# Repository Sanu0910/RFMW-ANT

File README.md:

# RFMW-ANT: RF / Microwave Antenna Design Projects

RF / microwave antenna design projects, one folder per project under `projects/NN_name/`, built so each one can be **re-simulated, checked and fabricated**.

Tooling:
- EM simulation: [`docs/GDS2OPENEMS.md`](docs/GDS2OPENEMS.md) — openEMS FDTD + gds2openEMS, installed with `tools/install_gds2openems.sh`.
- EM simulation: [`docs/HERTZON.md`](docs/HERTZON.md) — Hertzon 3D full-wave FEM simulator (EMerge solver, MCP server), installed with `tools/install_hertzon.sh`.
- PCB: [`docs/KICAD_MCP.md`](docs/KICAD_MCP.md) — KiCad + KiCAD-MCP-Server headless, installed with `tools/install_kicad_mcp.sh`.
- Agentic CAD workspace: [`docs/BACKPLANE.md`](docs/BACKPLANE.md) — Backplane, installed with `tools/install_backplane.sh`.
- Reverse engineering: [`docs/REA.md`](docs/REA.md) — REA CLI/MCP, installed with `tools/install_rea.sh`.

## Projects

| # | Folder | Description | Band | Content |
|---|---|---|---|---|
| 01 | [`projects/01_xband-8way-msl-wpd-housing`](projects/01_xband-8way-msl-wpd-housing) | Machined housing CRL-XB-PD8-03 (V3) for the X-band 8-way microstrip Wilkinson divider on RO4350B 30 mil, 9 x H+S 23_SMA-50-0-272/133_N, BEL logo engraved | 8–12 GHz | base / lid with channel cage / gasket STEP, PCB V3 DXF (M2 holes) + Gerber/drill set, 2D channel-mode and Z0 checks, A3 drawings, report, BOM |
| 02 | [`projects/02_ls-crpa4-rf-module`](projects/02_ls-crpa4-rf-module) | CRL-LS-CRPA4: 4-ch active CRPA board (limiter + 2 LNA + 3 SAW per band, L1 + L2/L5 combined, NavIC S at lambda/2), combined L+S back cover for the BEL CRL 4-element L/S CRPA board | 1.16–1.61 / 2.49 GHz | Ø200 mm 4L PCB (DRC clean), fab package + BOM, combined back cover STEP, RF budget, drawings, design report |
| 03 | [`projects/03_crpa-processor-module`](projects/03_crpa-processor-module) | CRPA digitizer + anti-jam processor (power inversion / MVDR / STAP) behind the CRL-LS-CRPA4 antenna | 1.16–1.61 / 2.49 GHz | reference review, architecture options; GNSS_JAM_PRO v1.0 case (PocketSDR v2.3, CNC): STEP + drawings |
| 04 | [`projects/04_xband-msl-cal-line-baseplate`](projects/04_xband-msl-cal-line-baseplate) | Lightweight open base plates CRL-XB-CALP-15 / -65 for the X-band RO4350B MSL-SL-MSL THRU cal boards, 2 x H+S 23_SMA-50-0-272/133_N each (same as project 01) | 8–12 GHz | plate + assembly + exploded STEP, A3 CNC drawings with hole table, design report, BOM |

**Each project folder contains** `00_README.md` (what is where), `STATUS.md` (where it stands, open items, next step) and `CHANGELOG.md` (dated history).

## Quick start
Running locally (all tools + MCP servers) and pushing finished projects: see [`LOCAL_SETUP.md`](LOCAL_SETUP.md).

```bash
pip install -r docs/requirements.txt
```

## Conventions
[`docs/CONVENTIONS.md`](docs/CONVENTIONS.md) covers units, DXF layer naming, HFSS import, and how assumptions are flagged. The tool setup is in [`STATUS.md`](STATUS.md).

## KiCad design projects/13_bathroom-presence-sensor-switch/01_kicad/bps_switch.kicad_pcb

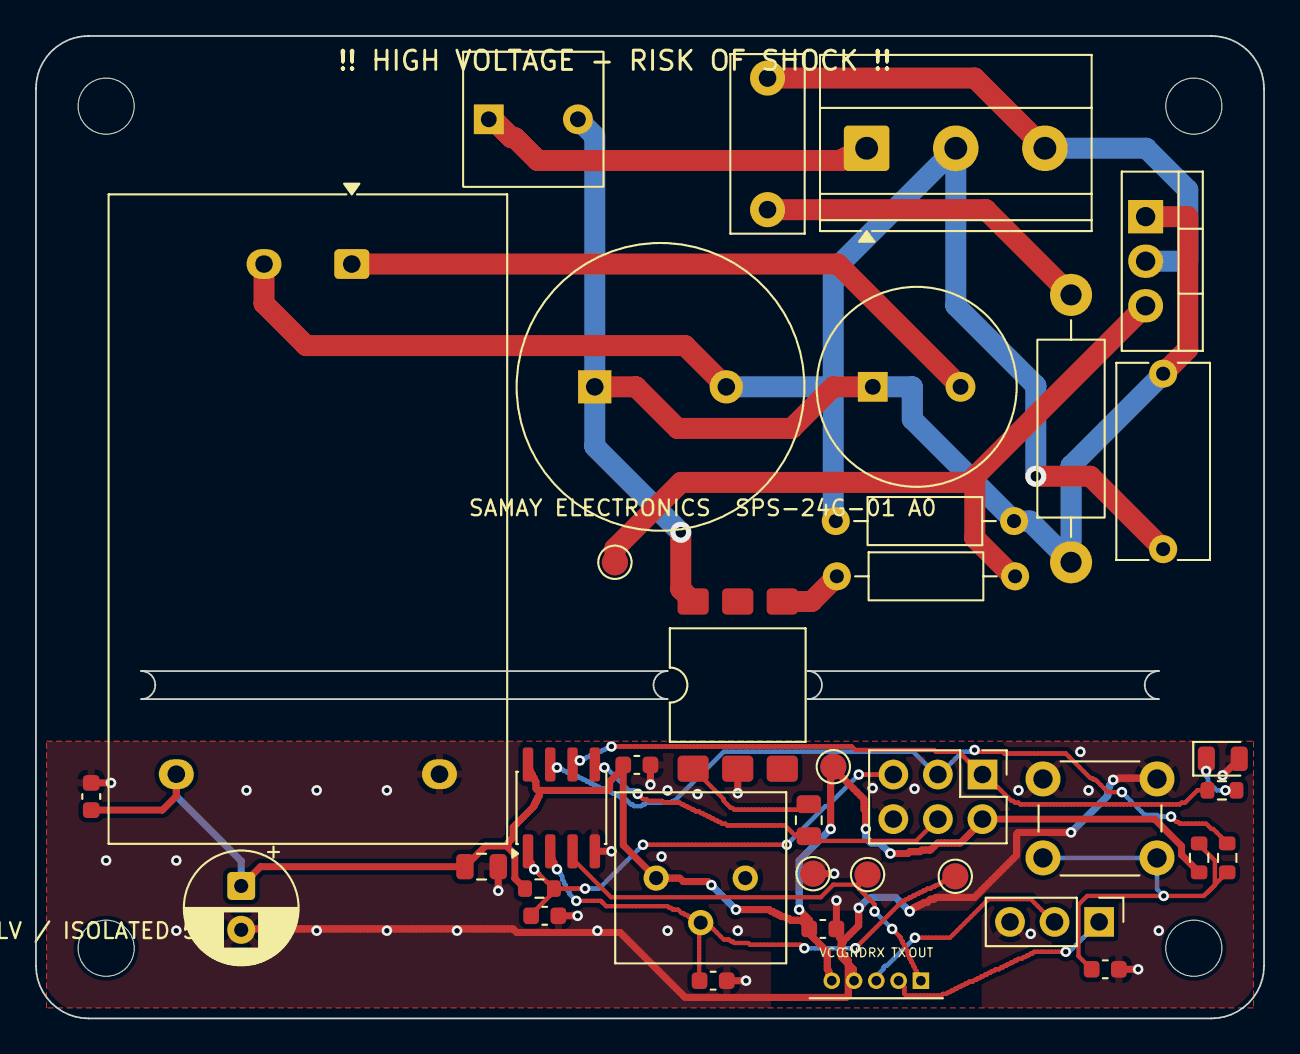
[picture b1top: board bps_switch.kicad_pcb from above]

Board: 2 copper layers, 70.0 x 56.0 mm, 41 parts (0 on the bottom side), 21 nets.

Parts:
C1, C4, C5, C6: 100nF; C_0603_1608Metric
C2: 10uF; C_0805_2012Metric
C3: 10nF; C_0603_1608Metric
CB1: 220uF/10V; CP_Radial_D6.3mm_P2.50mm
CB2: 100nF; C_0603_1608Metric
CS1: 10nF 400VAC; C_Rect_L10.0mm_W4.0mm_P7.50mm_FKS3_FKP3
CX1: 100nF X2; C_Rect_L11.0mm_W5.1mm_P10.00mm_MKT
D1: STATUS; LED_0805_2012Metric
F1: T500mA 250V; Fuse_TR5_P5.08mm
H1, H2, H3, H4: M3; MountingHole_3.2mm_M3
J1: L / N / LAMP; TerminalBlock_Phoenix_MKDS-1,5-3-5.08_1x03_P5.08mm_Horizont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
J2: AVR-ISP; PinHeader_2x03_P2.54mm_Vertical
J3: LD2410B; LD2410B_Module
J4: CFG UART; PinHeader_1x03_P2.54mm_Vertical
MOV1: 14D471K; Varistor_Disc_D16mm_P7.5mm
NTC1: 5D-9; NTC_Disc_D11mm_P5mm
PS1: HLK-PM01; Converter_ACDC_Hi-Link_HLK-PMxx
Q1: BTA16-600B; TO-220-3_Vertical
R1: 330R; R_0805_2012Metric
RB1: 1M; R_Axial_DIN0207_L6.3mm_D2.5mm_P10.16mm_Horizontal
RG1: 180R; R_Axial_DIN0207_L6.3mm_D2.5mm_P10.16mm_Horizontal
RL1: 1k; R_0603_1608Metric
RP1: 10k; R_0603_1608Metric
RR1: 10k; R_0603_1608Metric
RS1: 100R 2W; R_Axial_DIN0411_L9.9mm_D3.6mm_P15.24mm_Horizontal
RS2: 1k; R_0603_1608Metric
RV1: 10k; Potentiometer_Bourns_3386P_Vertical
SW1: OVERRIDE; SW_PUSH_6mm
TP1: +5V; TestPoint_Pad_D1.5mm
TP2: GND; TestPoint_Pad_D1.5mm
TP3: TRIAC_G; TestPoint_Pad_D1.5mm
TP4: RADAR_OUT; TestPoint_Pad_D1.5mm
TP5: DELAY_ADJ; TestPoint_Pad_D1.5mm
U1: ATtiny13A-SU; SOIC-8_3.9x4.9mm_P1.27mm
U2: MOC3063; SMDIP-6_W9.53mm_Clearance8mm

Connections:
+5V: C1.1, C2.1, C4.1, C5.1, CB1.1, J2.2, J3.5, PS1.4, RP1.1, RR1.1, RV1.1, TP1.1, U1.8
ACL_F: CX1.1, F1.2, MOV1.1, NTC1.1, Q1.1, RB1.1, RS1.1, U2.6
ACL_IN: F1.1, J1.1
ACN: CX1.2, J1.2, MOV1.2, PS1.2, RB1.2
BTN_SW: CB2.1, RP1.2, RS2.1, SW1.1
DELAY_ADJ: C6.1, RV1.2, TP5.1, U1.2
GND: C1.2, C2.2, C3.2, C4.2, C5.2, C6.2, CB1.2, CB2.2, D1.2, J2.6, J3.4, J4.3, PS1.3, RV1.3, SW1.2, TP2.1, U1.4, U2.2
LAMP: CS1.2, J1.3, Q1.2
LED_A: D1.1, RL1.2
MISO: J2.1, RL1.1, U1.6
MOSI: J2.4, R1.1, U1.5
OPTO_A: R1.2, U2.1
PSU_L: NTC1.2, PS1.1
RADAR_OUT: J3.1, TP4.1, U1.3
RADAR_RX: J3.3, J4.2
RADAR_TX: J3.2, J4.1
RESET: C3.1, J2.5, RR1.2, U1.1
SCK: J2.3, RS2.2, U1.7
SNUB_M: CS1.1, RS1.2
TRIAC_G: Q1.3, RG1.2, TP3.1
TRIAC_MT: RG1.1, U2.4

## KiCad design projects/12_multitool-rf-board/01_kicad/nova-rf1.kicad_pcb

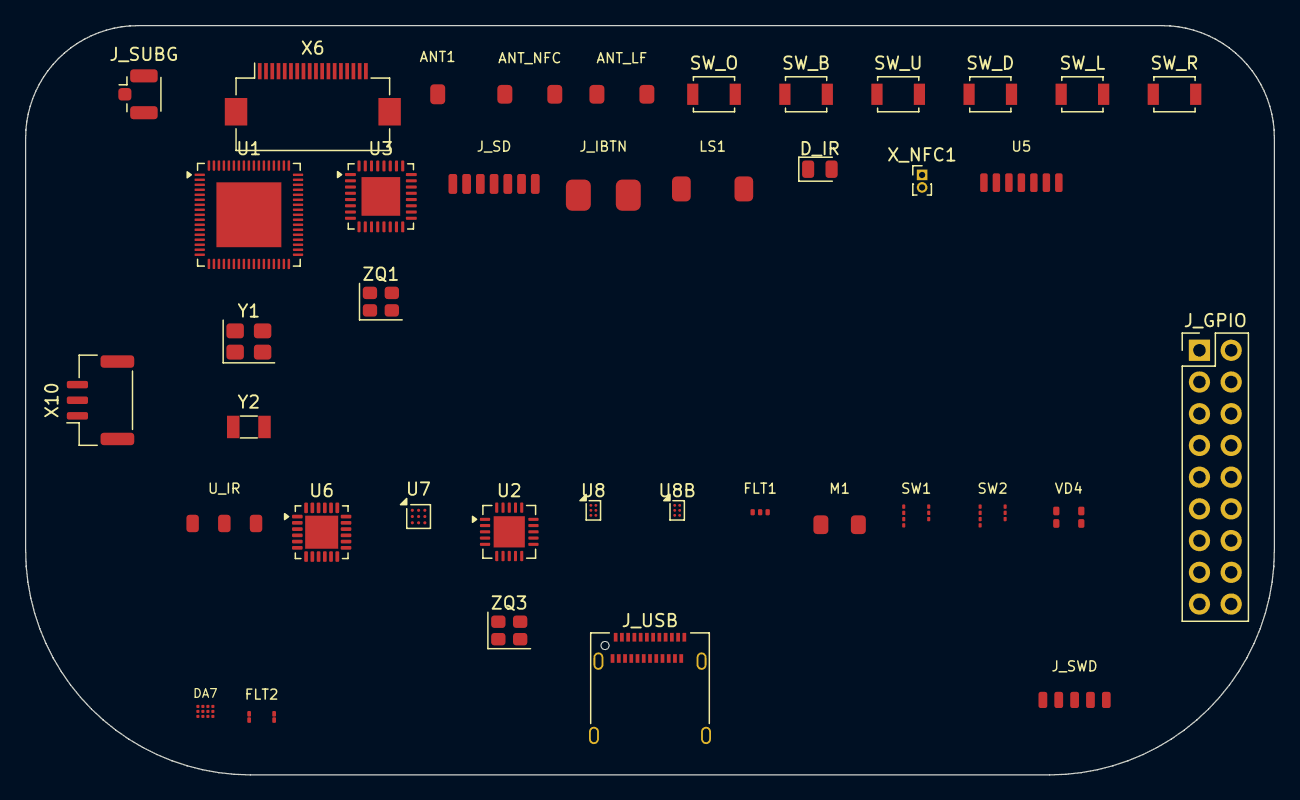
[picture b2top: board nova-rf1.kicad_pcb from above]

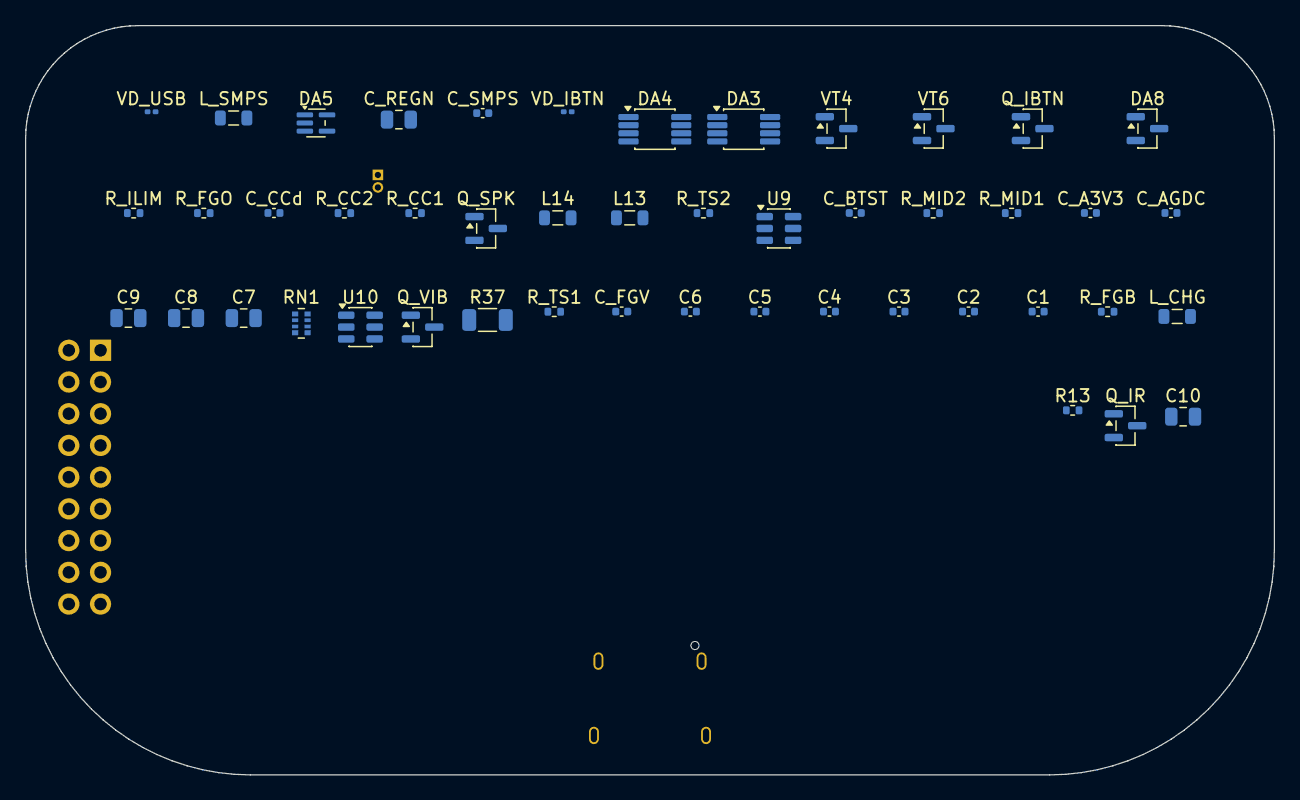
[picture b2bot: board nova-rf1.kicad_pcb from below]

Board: 4 copper layers, 100.0 x 60.0 mm, 87 parts (47 on the bottom side), 104 nets, no tracks yet.

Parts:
ANT1: 2.4GHz; Antenna_Chip
ANT_LF: 125kHz coil; RFID_125k_Coil
ANT_NFC: 13.56MHz loop; NFC_Loop_Antenna
C1, C2, C3, C4, C5, C6: 100nF; C_0402_1005Metric
C7, C8, C9, C10: 10uF; C_0805_2012Metric
C_A3V3: 1uF; C_0402_1005Metric
C_AGDC: 1uF; C_0402_1005Metric
C_BTST: 47nF; C_0402_1005Metric
C_CCd: 100nF; C_0402_1005Metric
C_FGV: 2.2uF; C_0402_1005Metric
C_REGN: 4.7uF; C_0805_2012Metric
C_SMPS: 2.2uF; C_0402_1005Metric
DA3, DA4: LMV358; VSSOP-8_3x3mm_P0.65mm
DA5: LMV331; SOT-353_SC-70-5
DA7: LP5562; LP5562_DSBGA12
DA8: RS3221-3.3; SOT-23
D_IR: IR LED x3; LED_0805_2012Metric
FLT1: BLE filter; RF_filter
FLT2: balun; Johanson_0310_Balun
J_GPIO: header 2x9; PinHeader_2x09_P2.54mm_Vertical
J_IBTN: iButton; iButton_Contacts
J_SD: microSD; microSD_7p
J_SUBG: ANT; U.FL_Hirose_U.FL-R-SMT-1_Vertical
J_SWD: SWD; TagConnect_TC2030
J_USB: USB-C; USB_C_Receptacle_Amphenol_12401610E4-2A
L13, L14: 470nH; L_0805_2012Metric
LS1: speaker; Speaker_2p
L_CHG: 2.2uH; L_0805_2012Metric
L_SMPS: 10uH; L_0805_2012Metric
M1: vibro; Vibro_2p
Q_IBTN: 1W driver; SOT-23
Q_IR: drive; SOT-23
Q_SPK: drive; SOT-23
Q_VIB: drive; SOT-23
R13: 56k; R_0402_1005Metric
R37: 10m; R_1206_3216Metric
RN1: 51x4; R_Array_Convex_4x0402
R_CC1, R_CC2: 5.1k; R_0402_1005Metric
R_FGB: 10k; R_0402_1005Metric
R_FGO: 10k; R_0402_1005Metric
R_ILIM: 1.1k; R_0402_1005Metric
R_MID1, R_MID2: 33k; R_0402_1005Metric
R_TS1: 5.23k; R_0402_1005Metric
R_TS2: 30.31k; R_0402_1005Metric
SW1, SW2: RFswitch; RF_Switch_TSNP9
SW_B: tact; SW_SPST_B3U-1000P
SW_D: tact; SW_SPST_B3U-1000P
SW_L: tact; SW_SPST_B3U-1000P
SW_O: tact; SW_SPST_B3U-1000P
SW_R: tact; SW_SPST_B3U-1000P
SW_U: tact; SW_SPST_B3U-1000P
U1: STM32WB55RG; QFN-68-1EP_8x8mm_P0.4mm_EP5.2x5.2mm
U2: CC1101; QFN-20-1EP_4x4mm_P0.5mm_EP2.5x2.5mm
U3: ST25R3916; QFN-32-1EP_5x5mm_P0.5mm_EP3.1x3.1mm
U5: ST7565R; Display_ST7565_FFC
U6: BQ25896; QFN-24-1EP_4x4mm_P0.5mm_EP2.65x2.65mm
U7: BQ27220; BGA-9_1.6x1.6mm_Layout3x3_P0.5mm
U8, U8B: LM3281; Texas_DSBGA-6_0.76x1.16mm_Layout2x3_P0.4mm
U9: loadsw; SOT-23-6
U10: ESD; SOT-23-6
U_IR: IR RX; TSOP_IR_3p
VD4: RGB LED; LED_RGB_4p
VD_IBTN: ESD; R_0201_0603Metric
VD_USB: ESD; R_0201_0603Metric
VT4: coildrv P; SOT-23
VT6: coildrv N; SOT-23
X6: FFC 18p; Hirose_FH12-18S-0.5SH_1x18-1MP_P0.50mm_Horizontal
X10: BAT+NTC; JST_GH_SM03B-GHS-TB_1x03-1MP_P1.25mm_Horizontal
X_NFC1: ANT conn; PinHeader_1x02_P1.00mm_Vertical
Y1: 32MHz; Crystal_SMD_3225-4Pin_3.2x2.5mm
Y2: 32.768kHz; Crystal_SMD_3215-2Pin_3.2x1.5mm
ZQ1: 27.12MHz; Crystal_SMD_2520-4Pin_2.5x2.0mm
ZQ3: 26MHz; Crystal_SMD_2520-4Pin_2.5x2.0mm

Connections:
+3V3: C1.1, C2.1, C3.1, C7.1, DA7.A2, DA7.C3, J_GPIO.1, J_SD.VDD, J_SWD.VCC, L13.2, SW1.VDD, SW2.VDD, U1.1, U1.13, U1.14, U1.30, U1.33, U1.44, U1.45, U1.55, U1.68, U2.4, U2.9, U2.11, U2.14, U2.15, U2.18, U3.1, U3.3, U3.7, U3.8, U3.9, U3.10, U3.11, U3.14, U5.VDD, U8.A1, U8.C1, U9.1, U_IR.VS, VD4.A
+3V3_EXT: L14.2, U8B.A1, X6.3
+3V3_PERIPH: C4.1, C10.1, U9.6
A3V3: C_A3V3.1, DA3.8, DA4.8, DA5.5, DA8.2, R_MID1.1
BLE_ANT: ANT1.1, FLT1.OUT
BTN_BACK: SW_B.1, U1.2
BTN_DOWN: SW_D.1, U1.50
BTN_LEFT: SW_L.1, U1.29
BTN_OK: SW_O.1, U1.5
BTN_RIGHT: SW_R.1, U1.46
BTN_UP: SW_U.1, U1.28
CC1101_CS: U1.61, U2.7
CC1101_GDO0: U1.16, U2.6
CC_DCOUPL: C_CCd.1, U2.5
CC_RBIAS: R13.1, U2.17
CC_XO1: U2.8, ZQ3.1
CC_XO2: U2.10, ZQ3.2
CHG_BTST: C_BTST.2, U6.21
CHG_ILIM: R_ILIM.1, U6.10
CHG_REGN: C_REGN.1, R_TS1.1, U6.22
CHG_SW: C_BTST.1, L_CHG.1, U6.19, U6.20
CHG_TS: R_TS1.2, R_TS2.1, U6.11
DISP_CS: U1.59, U5.CS
DISP_DI: U1.39, U5.A0
DISP_RST: U1.38, U5.RST
EXT_PA4: J_GPIO.4, U1.19
EXT_PA6: J_GPIO.3, U1.21
EXT_PA7: J_GPIO.2, U1.22
EXT_PB2: J_GPIO.6, U1.27
EXT_PB3: J_GPIO.5, U1.63
EXT_PC0: J_GPIO.9, U1.9
EXT_PC1: J_GPIO.8, U1.10
EXT_PC3: J_GPIO.7, U1.12
FG_BIN: R_FGB.1, U7.B1
FG_GPOUT: R_FGO.1, U7.A1
FG_VDD: C_FGV.1, R_FGO.2, U7.B3
GND: C1.2, C2.2, C3.2, C4.2, C5.2, C6.2, C7.2, C8.2, C9.2, C10.2, C_A3V3.2, C_AGDC.2, C_CCd.2, C_FGV.2, C_REGN.2, C_SMPS.2, DA3.4, DA4.4, DA5.2, DA7.B1, DA7.B2, DA7.B3, DA8.1, D_IR.1, FLT1.GND, FLT2.GND, J_GPIO.18, J_IBTN.GND, J_SD.VSS, J_SUBG.2, J_SWD.GND, J_USB.A1, J_USB.S1, LS1.-, M1.-, Q_IBTN.2, Q_IR.2, Q_SPK.2, Q_VIB.2, R13.2, R_CC1.2, R_CC2.2, R_FGB.2, R_ILIM.2, R_MID2.2, R_TS2.2, SW1.GND, SW2.GND, SW_B.2, SW_D.2, SW_L.2, SW_O.2, SW_R.2, SW_U.2, U1.32, U1.42, U1.69, U2.16, U2.19, U2.21, U3.6, U3.12, U3.16, U3.20, U3.21, U3.26, U3.33, U5.VSS, U6.9, U6.17, U6.18, U6.25, U7.B2, U7.C2, U8.C2, U8B.C2, U9.2, U10.2, U_IR.GND, VD_IBTN.2, VD_USB.2, VT6.2, X6.6, X6.8, X10.3
HSE_IN: U1.35, Y1.1
HSE_OUT: U1.34, Y1.2
I2C_PWR_SCL: DA7.C2, J_GPIO.15, U1.24, U6.5, U7.A3
I2C_PWR_SDA: DA7.C1, J_GPIO.14, U1.51, U6.6, U7.A2
IBTN: J_IBTN.DATA, Q_IBTN.1, U1.48, VD_IBTN.1, X6.14
IR_LED_A: D_IR.2, Q_IR.3
IR_RX: U1.15, U_IR.OUT, X6.17
IR_TX: Q_IR.1, U1.7, X6.16
LED_B: DA7.A4, VD4.B
LED_G: DA7.B4, VD4.G
LED_R: DA7.C4, VD4.R
LF_A1: DA3.1, DA3.5
LF_A2: DA3.7, DA4.3
LF_A3: DA4.1, DA4.5
LF_COIL_P: ANT_LF.1, VT4.3, VT6.3
LF_ENV: DA4.7, DA5.1
LF_MID: DA3.2, DA5.3, R_MID1.2, R_MID2.1
LF_RX: ANT_LF.2, DA3.3
LSE_IN: U1.3, Y2.1
LSE_OUT: U1.4, Y2.2
NFC_AGDC: C_AGDC.1, U3.24
NFC_ANT_N: ANT_NFC.2, X_NFC1.2
NFC_ANT_P: ANT_NFC.1, X_NFC1.1
NFC_CS: RN1.4, U1.40, U3.29, X6.4
NFC_XTAL1: U3.5, ZQ1.1
NFC_XTAL2: U3.4, ZQ1.2
NRST: J_SWD.NRST, U1.8
PERIPH_EN: U1.18, U8B.C1, U9.3
RFID_CARRIER: U1.17, U3.27, X6.12, X6.18
RFID_CARRIER_OUT: U1.57, VT4.1, X6.11
RFID_RF_IN: DA5.4, U1.26, X6.5
RF_SW_0: SW1.V1, SW2.V1, U1.25
RF_SW_1: SW1.V2, SW2.V2
SD_CD: J_SD.CD, U1.58
SD_CS: J_SD.CS, U1.60
SMPS_FB: C_SMPS.1, L_SMPS.2, U1.41
SMPS_LX: L_SMPS.1, U1.43
SPEAKER: Q_SPK.1, U1.6, X6.15
SPI_D_MISO: J_SD.DO, U1.11
SPI_D_MOSI: J_SD.DI, U1.49, U5.SI
SPI_D_SCK: J_SD.CLK, U1.62, U5.SCL
SPI_R_MISO: RN1.2, U1.64, U2.2, U3.32, X6.9
SPI_R_MOSI: RN1.3, U1.65, U2.20, U3.31, X6.13
SPI_R_SCK: RN1.1, U1.20, U2.1, U3.30, X6.7
SPK_DRV: LS1.+, Q_SPK.3
SUBG_ANT: J_SUBG.1, SW2.RFin
SUBG_F1: SW1.RF1, SW2.RF1
SUBG_F2: SW1.RF2, SW2.RF2
SUBG_RF_N: FLT2.BAL2, U2.13
SUBG_RF_P: FLT2.BAL1, U2.12
SUBG_SE: FLT2.UNBAL, SW1.RFin
SWCLK: J_GPIO.10, J_SWD.SWCLK, U1.56
SWDIO: J_GPIO.11, J_SWD.SWDIO, U1.54
SW_L13: L13.1, U8.B2
SW_L14: L14.1, U8B.B2
UART_RX: J_GPIO.13, U1.67
UART_TX: J_GPIO.12, U1.66
USB_CC1: J_USB.A5, R_CC1.1
USB_CC2: J_USB.B5, R_CC2.1
USB_DM: J_USB.A7, U1.52, U10.1, U10.6, VD_USB.1
USB_DP: J_USB.A6, U1.53, U10.3, U10.4
VBAT: C6.1, C9.1, R37.1, U6.13, U6.14, U7.C3, X10.1
VBAT_SNS: R37.2, U7.C1
VBUS: J_GPIO.16, J_USB.A4, U6.1, U10.5
VIBRO: J_GPIO.17, Q_VIB.1, U1.23, X6.10
VIBRO_DRV: M1.+, Q_VIB.3
VSYS: C5.1, C8.1, DA8.3, L_CHG.2, U6.15, U6.16, U8.A2, U8.B1, U8B.A2, U8B.B1, VT4.2, X6.1, X6.2

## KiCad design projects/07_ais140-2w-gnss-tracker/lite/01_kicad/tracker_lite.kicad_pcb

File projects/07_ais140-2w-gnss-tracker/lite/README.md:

# Samay Track Lite (preliminary)

A low-cost 4G Cat-1 + 2G bike tracker. **Not designed yet.** This folder holds the plan, the preliminary BOM and the poster.

| File | Content |
|---|---|
| `LITE_BOM_preliminary.csv` | Candidate parts with estimated 1k prices (≈ ₹1,362 per unit) |
| `poster_lite.html` / `SamayTrackLite_poster.png` / `.pdf` | Launch poster (₹3,499 incl. year 1, then ₹999/yr) |
| `../premium/07_marketing/SamayTrack_Lite_Plan.pdf` | 3-page plan: design, cost, price, money, timeline |

## BOM summary (estimate at 1,000 pcs, INR, excl. GST)

| Group | Main parts | ₹ |
|---|---|---|
| Modules | A7672S LTE Cat-1 + GSM (runs the firmware) · Quectel L76K GPS + BeiDou | 780 |
| ICs | LIS2DH12 accelerometer · LMR16010 60 V buck · BQ21040 charger · TLV75533 LDO · W25Q32 flash | 151 |
| Protection + I/O | SMBJ33CA TVS · reverse-polarity MOSFET · PTC fuse · SIM ESD · input clamps · relay MOSFET · LEDs | 35 |
| Connectors | nano-SIM, battery, harness, IPEX | 26 |
| Antennas | 25 mm GNSS ceramic patch · LTE FPC | 70 |
| Battery | 300 mAh Li-po with PCM (BIS registered) | 55 |
| Passives | ≈ 60 R/C/L + 2× 220 µF bulk caps for 2G bursts | 45 |
| PCB + SMT | 2-layer ≈ 50 × 35 mm, single-sided | 65 |
| Box build | IP65 enclosure, 4-wire harness with fuse, packaging | 135 |
| **Total** | | **≈ 1,362** |

Options:
- NavIC GNSS: + ₹300–400
- SOS push-button: + ₹25
- MFF2 eSIM instead of the nano-SIM holder

Prices are typical distributor or China-sourcing prices from memory, not quotes. Get real quotes before you commit.

**Design note:** in 2G the modem draws ≈ 2 A peaks, so the power path needs the battery plus the bulk capacitors. Size the buck and the charger for that.

Regenerate the poster (render taller and crop, because the headless window is ≈ 90 px shorter than `--window-size`):

    chrome --headless=new --force-device-scale-factor=2 --window-size=1200,1760 --screenshot=raw.png poster_lite.html   # crop to 2400 × 3280
    chrome --headless=new --no-pdf-header-footer --print-to-pdf=SamayTrackLite_poster.pdf poster_lite.html

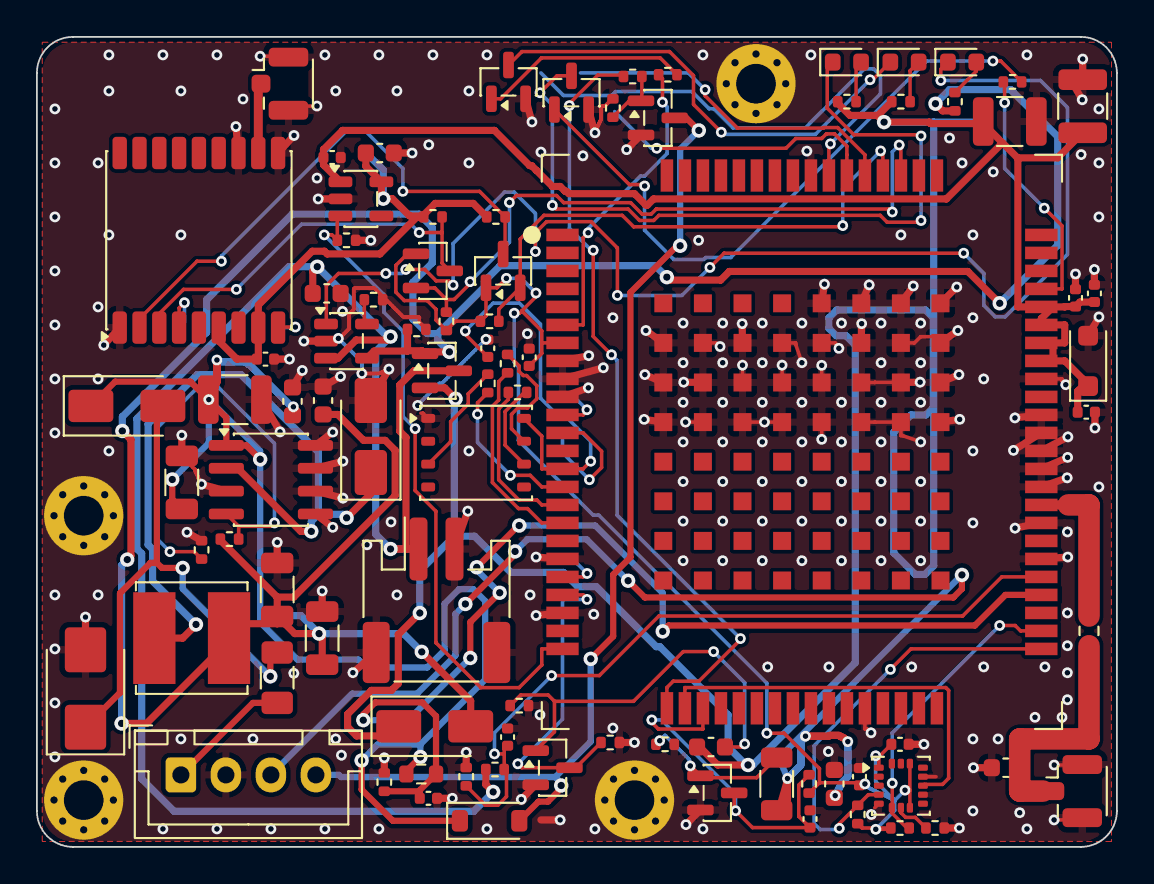
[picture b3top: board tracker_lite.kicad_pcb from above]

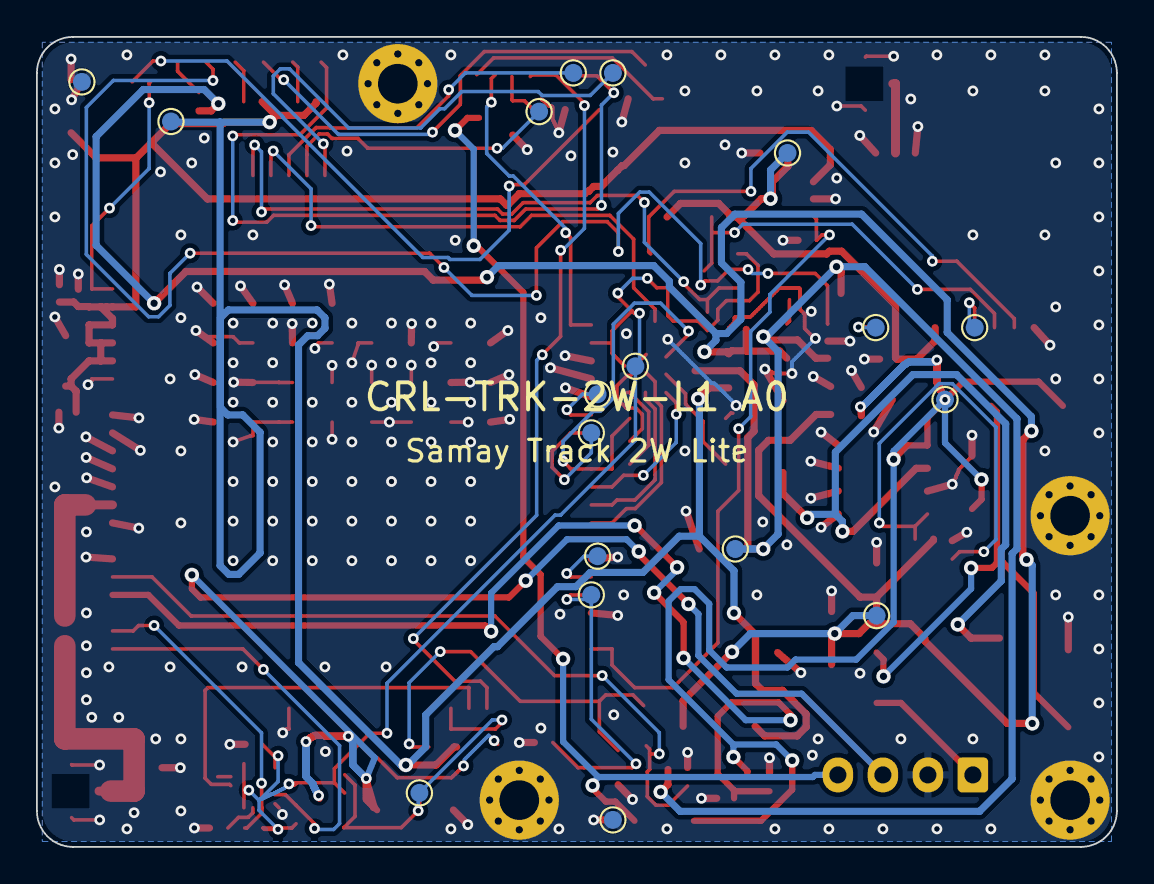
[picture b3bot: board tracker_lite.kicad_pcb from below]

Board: 2 copper layers, 60.0 x 45.0 mm, 109 parts (18 on the bottom side), 59 nets.

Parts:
C1: 10uF/50V; C_1210_3225Metric
C2: 4.7uF/50V; C_1206_3216Metric
C3: 100nF/50V; C_0603_1608Metric
C4, C5: 22uF/10V; C_1206_3216Metric
C6, C7: 4.7uF/10V; C_0603_1608Metric
C8, C9: 100uF/6.3V; C_1210_3225Metric
C10, C13, C14, C17, C22, C26: 100nF; C_0402_1005Metric
C11: 33pF; C_0402_1005Metric
C12: 10pF; C_0402_1005Metric
C15, C20, C27: 1uF; C_0402_1005Metric
C16, C21: 10uF/10V; C_0603_1608Metric
C19: DNP; C_0603_1608Metric
C28: 10nF/100V; C_0603_1608Metric
C29: 1nF; C_0402_1005Metric
D1: SMBJ24CA; D_SMB
D2, D3, D4: SS34; D_SMA
D5: SMF5.0A; D_SOD-123F
D6: 1N4148W; D_SOD-123
D7: YELLOW; LED_0603_1608Metric
D8: GREEN; LED_0603_1608Metric
D9: RED; LED_0603_1608Metric
F1: 2A; Fuse_1206_3216Metric
H1, H2, H3, H4: M2; MountingHole_2.2mm_M2_Pad_Via
J1: VEHICLE 4P; JST_XH_B4B-XH-A_1x04_P2.50mm_Vertical
J2: LiPo 300mAh; JST_PH_S2B-PH-SM4-TB_1x02-1MP_P2.00mm_Horizontal
J4: LTE ANT; U.FL_Hirose_U.FL-R-SMT-1_Vertical
J5: GNSS ANT; U.FL_Hirose_U.FL-R-SMT-1_Vertical
L1: 22uH; L_Bourns_SRN6045TA
Q1: AO3401A; SOT-23
Q2: 2N7002; SOT-23
Q3, Q4: BSS138; SOT-23
Q5, Q7, Q8: MMBT3904; SOT-23
Q6: AO3400A; SOT-23
R1: 2.61k; R_0402_1005Metric
R2, R30, R32, R33: 1k; R_0402_1005Metric
R3: 6.8k; R_0402_1005Metric
R4, R8, R15, R26, R28: 100k; R_0402_1005Metric
R5: 1M; R_0603_1608Metric
R6: 33k; R_0402_1005Metric
R7: 300k; R_0402_1005Metric
R9: 220k; R_0402_1005Metric
R10: 0R; R_0402_1005Metric
R11, R12, R13: 22R; R_0402_1005Metric
R14: 0R; R_0603_1608Metric
R18, R19, R20, R21, R25, R34: 10k; R_0402_1005Metric
R22, R23, R29, R31: 4.7k; R_0402_1005Metric
R24: 47k; R_1206_3216Metric
R27: 100R; R_0402_1005Metric
TP1: MDM_PWRKEY; TestPoint_Pad_D1.0mm
TP2: MDM_RESET_N; TestPoint_Pad_D1.0mm
TP3: MDM_USB_VBUS; TestPoint_Pad_D1.0mm
TP4: MDM_USB_DP; TestPoint_Pad_D1.0mm
TP5: MDM_USB_DM; TestPoint_Pad_D1.0mm
TP6: MDM_DBG_TX; TestPoint_Pad_D1.0mm
TP7: MDM_DBG_RX; TestPoint_Pad_D1.0mm
TP8: GNSS_RST_N; TestPoint_Pad_D1.0mm
TP9: GNSS_1PPS; TestPoint_Pad_D1.0mm
TP10: VIN_PROT; TestPoint_Pad_D1.0mm
TP11: V4_BUCK; TestPoint_Pad_D1.0mm
TP12: VSYS; TestPoint_Pad_D1.0mm
TP13: VBAT; TestPoint_Pad_D1.0mm
TP14: MDM_1V8; TestPoint_Pad_D1.0mm
TP15: +3V3_GNSS; TestPoint_Pad_D1.0mm
TP16, TP17: GND; TestPoint_Pad_D1.0mm
TP18: IGN_DET_N; TestPoint_Pad_D1.0mm
U1: XL1509-ADJ; SOIC-8_3.9x4.9mm_P1.27mm
U2: MCP73831-2; SOT-23-5
U3: EC200U-CN; Quectel_EC200U_LCC-144
U5: L76K; Quectel_L76K
U6: AP2112K-3.3; SOT-23-5
U7: LIS3DH; LGA-16_3x3mm_P0.5mm_LayoutBorder3x5y
U8: MFF2 eSIM; MFF2_eSIM_DFN-8_6x5mm

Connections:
+3V3_GNSS: C21.1, C22.1, R19.1, R21.1, TP15.1, U5.6, U5.8, U6.5
ACC_INT: U3.26, U7.11
ACC_SA0: R34.1, U7.7
BUCK_FB: R1.2, R2.1, U1.4
BUCK_SW: D3.1, L1.1, U1.2
CHG_PROG: R3.1, U2.5
CHG_STAT: D9.1, U2.1
GND: C1.2, C2.2, C3.2, C4.2, C5.2, C6.2, C7.2, C8.2, C9.2, C10.2, C11.2, C12.2, C13.2, C14.2, C15.2, C17.2, C19.2, C20.2, C21.2, C22.2, C26.2, C27.2, C28.2, C29.2, D1.2, D3.2, D5.2, H1.1, H2.1, H3.1, H4.1, J1.2, J2.2, J2.MP, J4.2, J5.2, Q2.2, Q5.2, Q6.2, Q7.2, Q8.2, R2.2, R3.2, R4.2, R6.2, R8.2, R9.2, R10.2, R15.2, R25.2, R28.2, R34.2, TP16.1, TP17.1, U1.3, U1.5, U1.6, U1.7, U1.8, U2.2, U3.8, U3.9, U3.10, U3.19, U3.22, U3.36, U3.46, U3.48, U3.50, U3.51, U3.52, U3.53, U3.54, U3.56, U3.72, U3.85, U3.86, U3.87, U3.88, U3.89, U3.90, U3.91, U3.92, U3.93, U3.94, U3.95, U3.96, U3.97, U3.98, U3.99, U3.100, U3.101, U3.102, U3.103, U3.104, U3.105, U3.106, U3.107, U3.108, U3.109, U3.110, U3.111, U3.112, U5.1, U5.10, U5.12, U6.2, U7.5, U7.10, U7.12, U8.1
GNSS_1PPS: TP9.1, U5.4
GNSS_EN: R15.1, U3.24, U6.3
GNSS_RF: J5.1, U5.11
GNSS_RST_N: TP8.1, U5.9
GNSS_RXD: Q3.3, R19.2, U5.3
GNSS_TXD: Q4.3, R21.2, U5.2
I2C_SCL: R23.2, U3.41, U7.4
I2C_SDA: R22.2, U3.42, U7.6
IGN_B: Q5.1, R24.2, R25.1
IGN_DET_N: C29.1, Q5.3, R26.2, TP18.1, U3.27
IGN_RAW: C28.1, J1.3, R24.1
LED_CHG_A: D9.2, R33.2
LED_NET_A: D7.2, R30.2
LED_NET_K: D7.1, Q7.3
LED_PWR_A: D8.2, R32.2
LED_PWR_K: D8.1, Q8.3
LTE_RF: C19.1, J4.1, R14.2
LTE_RF_M: R14.1, U3.49
MDM_1V8: C15.1, C26.1, C27.1, Q3.1, Q4.1, R18.1, R20.1, R22.1, R23.1, R26.1, TP14.1, U3.7, U7.1, U7.8, U7.14
MDM_DBG_RX: TP7.1, U3.11
MDM_DBG_TX: TP6.1, U3.12
MDM_PWRKEY: Q2.3, R10.1, TP1.1, U3.21
MDM_RESET_N: TP2.1, U3.20
MDM_RX_1V8: Q4.2, R20.2, U3.68
MDM_STATUS: R31.1, U3.61
MDM_TX_1V8: Q3.2, R18.2, U3.67
MDM_USB_DM: TP5.1, U3.70
MDM_USB_DP: TP4.1, U3.69
MDM_USB_VBUS: TP3.1, U3.71
NET_B: Q7.1, R29.2
NET_STATUS: R29.1, U3.6
PWRKEY_G: C16.2, Q2.1, R9.1
RELAY_CTL: R27.1, U3.25
RELAY_G: Q6.1, R27.2, R28.1
RELAY_OUT: D6.2, J1.4, Q6.3
SIM_CLK: R12.2, U8.6
SIM_CLK_M: R12.1, U3.16
SIM_DATA: R11.2, U8.3
SIM_DATA_M: R11.1, U3.15
SIM_RST: R13.2, U8.7
SIM_RST_M: R13.1, U3.17
SIM_VDD: C17.1, U3.14, U8.8
STAT_B: Q8.1, R31.2
V4_BUCK: C4.1, C5.1, C6.1, D4.2, L1.2, Q1.1, R1.1, R4.1, R33.1, TP11.1, U2.4
VBAT: C7.1, J2.1, Q1.3, R7.1, TP13.1, U2.3
VBAT_SENSE: C14.1, R7.2, R8.1, U3.45
VIN_F: D1.1, D2.2, F1.2
VIN_PROT: C1.1, C2.1, C3.1, D2.1, D6.1, R5.1, TP10.1, U1.1
VIN_RAW: F1.1, J1.1
VIN_SENSE: C13.1, R5.2, R6.1, U3.44
VSYS: C8.1, C9.1, C10.1, C11.1, C12.1, C16.1, C20.1, D4.1, D5.1, Q1.2, R30.1, R32.1, TP12.1, U3.57, U3.58, U3.59, U3.60, U6.1

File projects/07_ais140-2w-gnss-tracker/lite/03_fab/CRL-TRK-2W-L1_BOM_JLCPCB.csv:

Comment,Designator,Footprint,LCSC Part #,Manufacturer Part Number
10uF/50V,C1,C_1210_3225Metric,,1210 MLCC X5R/X7R
4.7uF/50V,C2,C_1206_3216Metric,,1206 MLCC X5R/X7R
100nF/50V,C3,C_0603_1608Metric,,0603 MLCC X5R/X7R
22uF/10V,"C4,C5",C_1206_3216Metric,,1206 MLCC X5R/X7R
4.7uF/10V,"C6,C7",C_0603_1608Metric,,0603 MLCC X5R/X7R
100uF/6.3V,"C8,C9",C_1210_3225Metric,,1210 MLCC X5R/X7R
100nF,"C10,C13,C14,C17,C22,C26",C_0402_1005Metric,,0402 MLCC X5R/X7R
33pF,C11,C_0402_1005Metric,,0402 C0G 50V
10pF,C12,C_0402_1005Metric,,0402 C0G 50V
1uF,"C15,C20,C27",C_0402_1005Metric,,0402 MLCC X5R/X7R
10uF/10V,"C16,C21",C_0603_1608Metric,,0603 MLCC X5R/X7R
10nF,C23,C_0402_1005Metric,,0402 MLCC X5R/X7R
10nF/100V,C28,C_0603_1608Metric,,0603 MLCC X5R/X7R
1nF,C29,C_0402_1005Metric,,0402 MLCC X5R/X7R
SMBJ24CA,D1,D_SMB,,SMBJ24CA
SS34,"D2,D3,D4",D_SMA,,SS34
SMF5.0A,D5,D_SOD-123F,,SMF5.0A
1N4148W,D6,D_SOD-123,,1N4148W-7-F
YELLOW,D7,LED_0603_1608Metric,,KT-0603Y
GREEN,D8,LED_0603_1608Metric,,KT-0603G
RED,D9,LED_0603_1608Metric,,KT-0603R
2A,F1,Fuse_1206_3216Metric,,0466002.NRHF
VEHICLE 4P,J1,JST_XH_B4B-XH-A_1x04_P2.50mm_Vertical,,B4B-XH-A(LF)(SN)
LiPo 300mAh,J2,JST_PH_S2B-PH-SM4-TB_1x02-1MP_P2.00mm_Horizontal,,S2B-PH-SM4-TB(LF)(SN)
LTE ANT,J4,U.FL_Hirose_U.FL-R-SMT-1_Vertical,,U.FL-R-SMT-1(10)
GNSS ANT,J5,U.FL_Hirose_U.FL-R-SMT-1_Vertical,,U.FL-R-SMT-1(10)
22uH,L1,L_Bourns_SRN6045TA,,SRN6045TA-220M
47nH,L2,L_0402_1005Metric,,LQG15HS47NJ02D
AO3401A,Q1,SOT-23,,AO3401A
2N7002,Q2,SOT-23,,2N7002K-7
BSS138,"Q3,Q4",SOT-23,,BSS138
MMBT3904,"Q5,Q7,Q8",SOT-23,,MMBT3904
AO3400A,Q6,SOT-23,,AO3400A
2.61k,R1,R_0402_1005Metric,,0402 1% thick film
1k,"R2,R30,R32,R33",R_0402_1005Metric,,0402 1% thick film
6.8k,R3,R_0402_1005Metric,,0402 1% thick film
100k,"R4,R8,R15,R26,R28",R_0402_1005Metric,,0402 1% thick film
1M,R5,R_0603_1608Metric,,0603 1% thick film
33k,R6,R_0402_1005Metric,,0402 1% thick film
300k,R7,R_0402_1005Metric,,0402 1% thick film
220k,R9,R_0402_1005Metric,,0402 1% thick film
22R,"R11,R12,R13",R_0402_1005Metric,,0402 1% thick film
0R,R14,R_0603_1608Metric,,0603 0R jumper
10R,R16,R_0402_1005Metric,,0402 1% thick film
10k,"R18,R19,R20,R21,R25,R34",R_0402_1005Metric,,0402 1% thick film
4.7k,"R22,R23,R29,R31",R_0402_1005Metric,,0402 1% thick film
47k,R24,R_1206_3216Metric,,1206 1% thick film
100R,R27,R_0402_1005Metric,,0402 1% thick film
XL1509-ADJ,U1,SOIC-8_3.9x4.9mm_P1.27mm,,XL1509-ADJE1
MCP73831-2,U2,SOT-23-5,,MCP73831T-2ACI/OT
EC200U-CN,U3,Quectel_EC200U_LCC-144,,EC200UCNAA-N05-SNNSA
L76K,U5,Quectel_L76K,,L76KB-A58
AP2112K-3.3,U6,SOT-23-5,,AP2112K-3.3TRG1
LIS3DH,U7,LGA-16_3x3mm_P0.5mm_LayoutBorder3x5y,,LIS3DHTR
MFF2 eSIM,U8,MFF2_eSIM_DFN-8_6x5mm,,"M2M MFF2 eUICC (operator-supplied, e.g. Jio / Airtel / Vi IoT)"

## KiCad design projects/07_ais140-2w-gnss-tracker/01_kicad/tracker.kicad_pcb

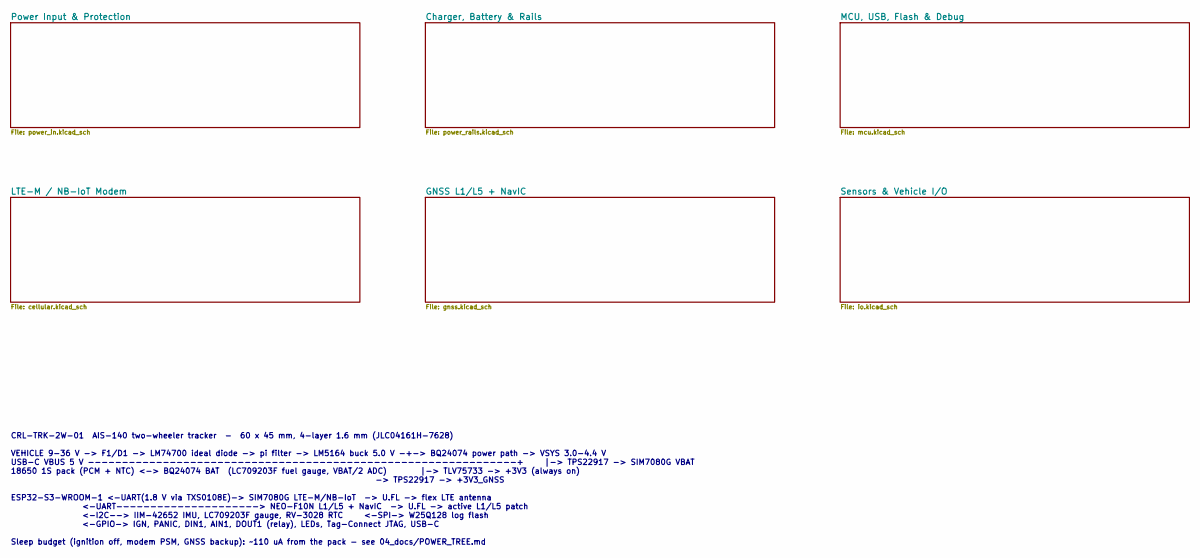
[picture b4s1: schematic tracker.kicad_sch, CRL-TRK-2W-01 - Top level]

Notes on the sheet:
CRL-TRK-2W-01 AIS-140 two-wheeler tracker - 60 x 45 mm, 4-layer 1.6 mm (JLC04161H-7628) VEHICLE 9-36 V -> F1/D1 -> LM74700 ideal diode -> pi filter -> LM5164 buck 5.0 V -+-> BQ24074 power path -> VSYS 3.0-4.4 V USB-C VBUS 5 V ---------------------------------------------------------------+ |-> TPS2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

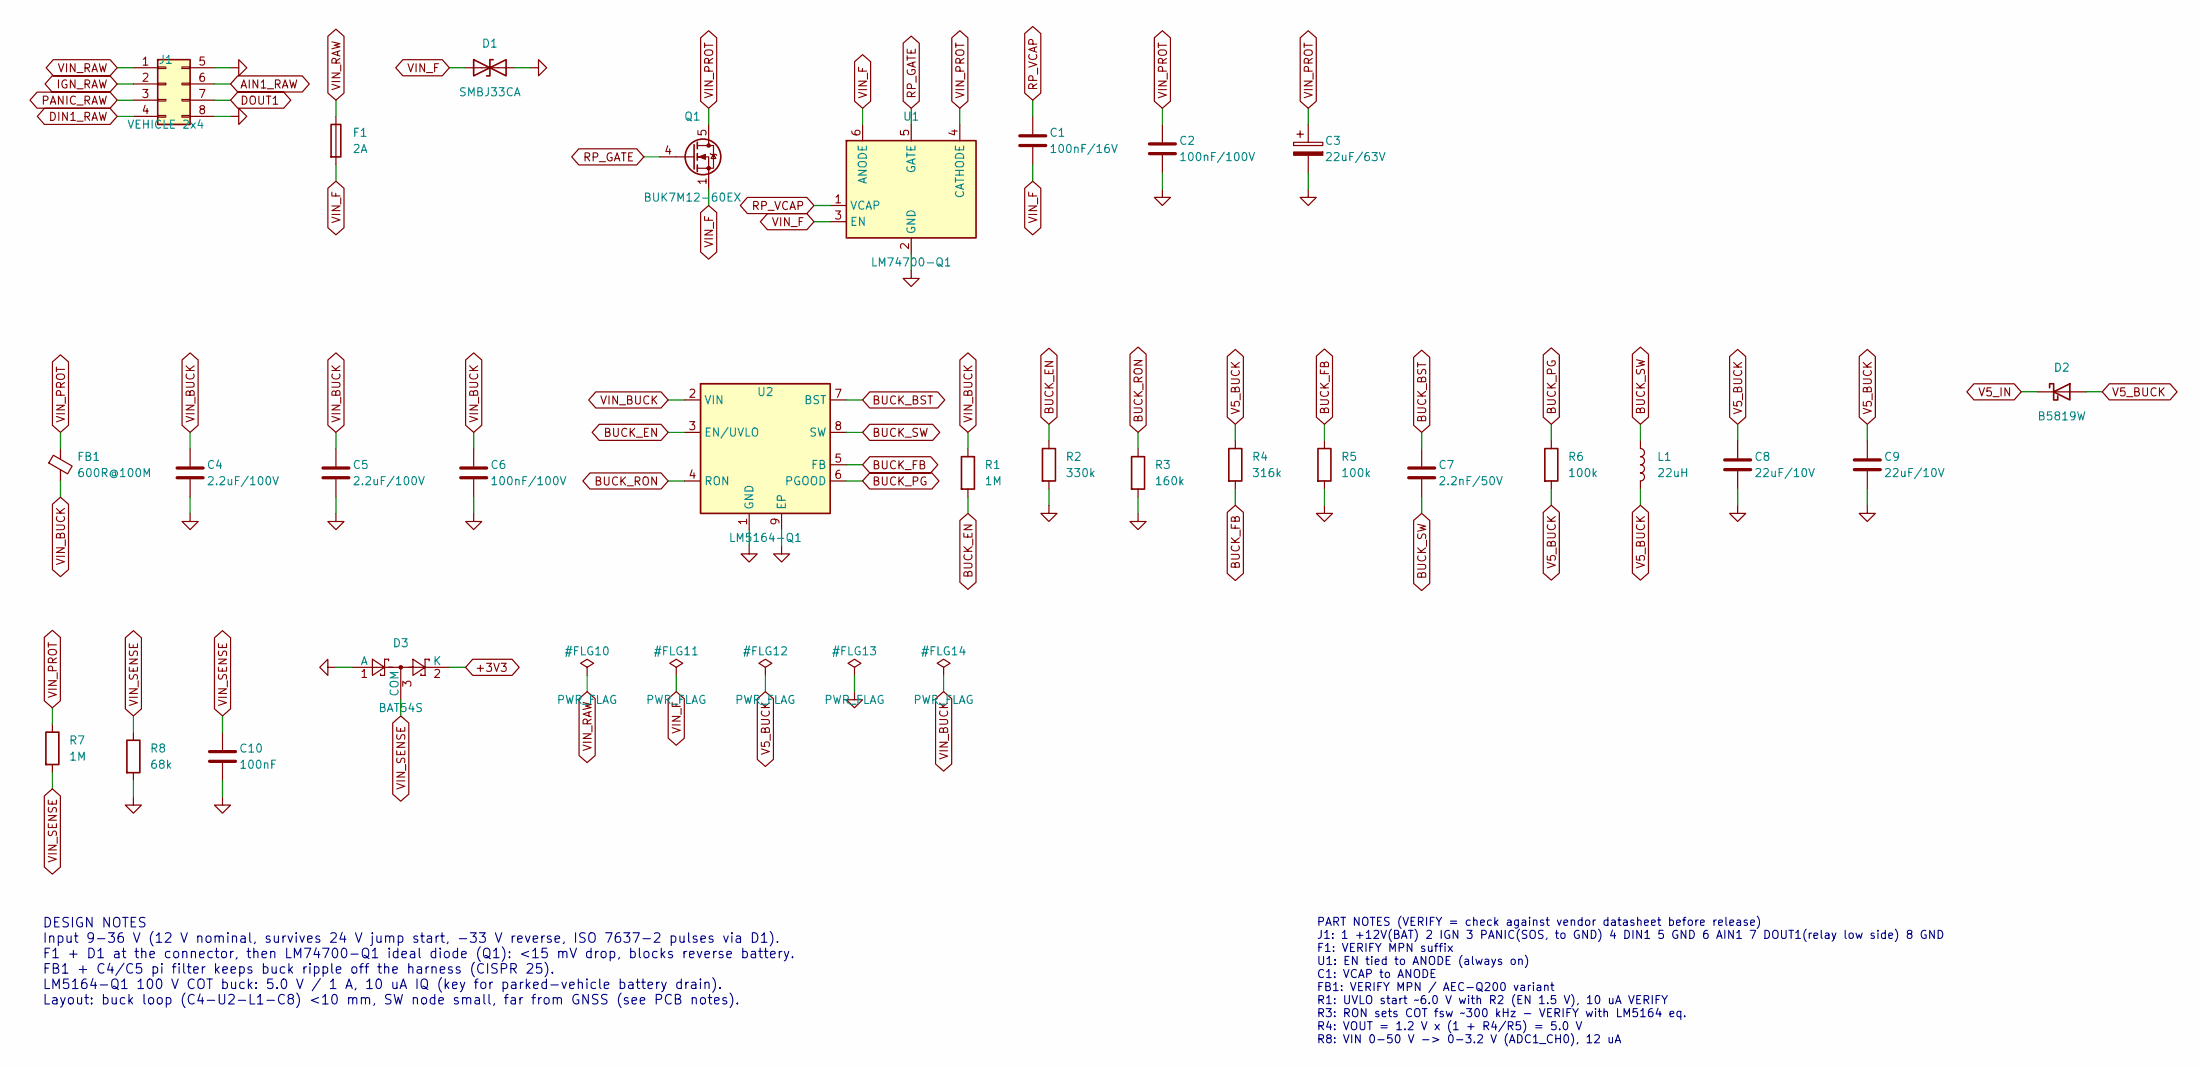
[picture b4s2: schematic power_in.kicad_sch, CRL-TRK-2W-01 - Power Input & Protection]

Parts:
C1: 100nF/16V; C_0603_1608Metric; MPN 0603 MLCC X7R/X5R, AEC-Q200
C2, C6: 100nF/100V; C_0603_1608Metric; MPN 0603 MLCC X7R/X5R, AEC-Q200
C3: 22uF/63V; CP_Elec_6.3x7.7; MPN EEE-FK1J220P
C4, C5: 2.2uF/100V; C_1210_3225Metric; MPN 1210 MLCC X7R/X5R, AEC-Q200
C7: 2.2nF/50V; C_0402_1005Metric; MPN 0402 MLCC X7R/X5R, AEC-Q200
C8, C9: 22uF/10V; C_1206_3216Metric; MPN 1206 MLCC X7R/X5R, AEC-Q200
C10: 100nF; C_0603_1608Metric; MPN 0603 MLCC X7R/X5R, AEC-Q200
D1: SMBJ33CA; D_SMB; MPN SMBJ33CA
D2: B5819W; D_SOD-123; MPN B5819W
D3: BAT54S; SOT-23; MPN BAT54S
F1: 2A; Fuse_1206_3216Metric; MPN 0466002.NRHF
FB1: 600R@100M; L_0805_2012Metric; MPN BLM21PG601SN1D
J1: VEHICLE 2x4; Molex_Micro-Fit_3.0_43045-0812_2x04_P3.00mm_Vertical; MPN 43045-0812
L1: 22uH; L_Bourns_SRN6045TA; MPN SRN6045TA-220M
Q1: BUK7M12-60EX; LFPAK33; MPN BUK7M12-60EX
R1: 1M; R_0603_1608Metric; MPN 0603 1% thick film, AEC-Q200
R2: 330k; R_0402_1005Metric; MPN 0402 1% thick film, AEC-Q200
R3: 160k; R_0402_1005Metric; MPN 0402 1% thick film, AEC-Q200
R4: 316k; R_0603_1608Metric; MPN 0603 1% thick film, AEC-Q200
R5: 100k; R_0402_1005Metric; MPN 0402 1% thick film, AEC-Q200
R6: 100k; R_0603_1608Metric; MPN 0603 1% thick film, AEC-Q200
R7: 1M; R_1206_3216Metric; MPN 1206 1% thick film, AEC-Q200
R8: 68k; R_0402_1005Metric; MPN 0402 1% thick film, AEC-Q200
U1: LM74700-Q1; SOT-23-6; MPN LM74700QDBVRQ1
U2: LM5164-Q1; HSOP-8-1EP_3.9x4.9mm_P1.27mm_EP2.41x3.1mm_ThermalVias; MPN LM5164QDDARQ1

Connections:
+3V3: D3.2 (K); also elsewhere on the board
AIN1_RAW: J1.6; also elsewhere on the board
BUCK_BST: C7.1, U2.7 (BST)
BUCK_EN: R1.2, R2.1, U2.3 (EN/UVLO)
BUCK_FB: R4.2, R5.1, U2.5 (FB)
BUCK_PG: R6.1, U2.6 (PGOOD)
BUCK_RON: R3.1, U2.4 (RON)
BUCK_SW: C7.2, L1.1, U2.8 (SW)
DIN1_RAW: J1.4; also elsewhere on the board
DOUT1: J1.7; also elsewhere on the board
GND: C2.2, C3.2, C4.2, C5.2, C6.2, C8.2, C9.2, C10.2, D1.2 (A2), D3.1 (A), J1.5, J1.8, R2.2, R3.2, R5.2, R8.2, U1.2 (GND), U2.1 (GND), U2.9 (EP); also elsewhere on the board
IGN_RAW: J1.2; also elsewhere on the board
PANIC_RAW: J1.3; also elsewhere on the board
RP_GATE: Q1.4 (G), U1.5 (GATE)
RP_VCAP: C1.1, U1.1 (VCAP)
V5_BUCK: C8.1, C9.1, D2.2 (A), L1.2, R4.1, R6.2
V5_IN: D2.1 (K); also elsewhere on the board
VIN_BUCK: C4.1, C5.1, C6.1, FB1.2, R1.1, U2.2 (VIN)
VIN_F: C1.2, D1.1 (A1), F1.2, Q1.1 (S), Q1.2 (S), Q1.3 (S), U1.3 (EN), U1.6 (ANODE)
VIN_PROT: C2.1, C3.1, FB1.1, Q1.5 (D), R7.1, U1.4 (CATHODE); also elsewhere on the board
VIN_RAW: F1.1, J1.1
VIN_SENSE: C10.1, D3.3 (COM), R7.2, R8.1; also elsewhere on the board

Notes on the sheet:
DESIGN NOTES Input 9-36 V (12 V nominal, survives 24 V jump start, -33 V reverse, ISO 7637-2 pulses via D1). F1 + D1 at the connector, then LM74700-Q1 ideal diode (Q1): <15 mV drop, blocks reverse battery. FB1 + C4/C5 pi filter keeps buck ripple off the harness (CISPR 25). LM5164-Q1 100 V COT buck: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
PART NOTES (VERIFY = check against vendor datasheet before release) J1: 1 +12V(BAT) 2 IGN 3 PANIC(SOS, to GND) 4 DIN1 5 GND 6 AIN1 7 DOUT1(relay low side) 8 GND F1: VERIFY MPN suffix U1: EN tied to ANODE (always on) C1: VCAP to ANODE FB1: VERIFY MPN / AEC-Q200 variant R1: UVLO start ~6.0 V with R2 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
